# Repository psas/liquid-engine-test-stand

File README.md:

# liquid-engine-test-stand

# Liquid Fuel Engine Test Stand (LFETS) Project Overview

  PSAS team members have already designed and built a [2.5 kN regeneratively cooled bipropellant (liquid oxygen and ethanol) rocket engine](https://github.com/psas/liquid-engine-capstone-2015). This engine design included a number of innovative features including fully parametric CAD design using python scripts and SolidWorks, direct metal laser sintering (DMLS) additive manufacturing by i3D manufacturing, direct spark ignition and pintle injection. Although the rocket engine itself has already been produced, much of the overall system complexity lies in the piping, control, and data acquisition systems which support it. This project intends to flesh out these systems in order to test the engine and its successors.

  The test stand will safely test current and PSAS future generation liquid fuel engines prior to integration into a flight vehicle. PSAS will use the stand to measure engine performance, liquid fuel and oxidizer flow rates, propellant mixing capabilities and other engine performance figures of merit. These tests will be performed remotely, using automated valve switching and data acquisition systems. The LFETS system is designed to be portable by truck, and will support propulsion testing of engines up to 10 kN of thrust. The project will be open-source and will utilize live web-based Jupyter notebook design documentation.

  The feed system uses a classic regulated pressure-fed thermodynamic cycle. Gaseous nitrogen is the pressurant. The LFETS system includes a welded thrust loading truss structure, propellant and pressurant supply tanks, and feed system flow componentry. The project also includes safety and Failure Mode Effects Analysis, and procedures for safe operation and transport.
The LFETS Electrical Ground Support Equipment (EGSE) will allow for the test stand to be controlled remotely. The test stand computer controls all actuators in the LFETS system, auto-sequences engine ignition, start, shutdown, pad-safing, and contingency procedures for any test exception, as well as receiving telemetry from sensors and instrumentation. The LFETS EGSE system is derived from the 3rd generation [PSAS launch tower computer](https://github.com/psas/launch-tower), which uses a BeagleBone Black microcontroller, the [Marionette open-source DAQ](https://marionette-daq.github.io/), and a custom “SCADA-like” GUI.

## Useful Links

[CAD Files](https://github.com/psas/liquid-engine-test-stand/tree/master/cad/Test%20Stand%20CAD%20Files/current%20assembly)

[CAD Guide](https://github.com/psas/liquid-engine-test-stand/blob/master/cad/CAD%20Guide.pdf)

[Bill of Materials](https://drive.google.com/open?id=1SeBntyje6zpfy1jSxysdBP59IyhFcIg6SvVT6w5Bf4Y)

[PID](https://github.com/psas/liquid-engine-test-stand/tree/master/PID)

[Capstone Class Work](https://github.com/psas/liquid-engine-test-stand/tree/master/2018-2019%20Capstone%20documentation/Class%20papers%20and%20presentations)

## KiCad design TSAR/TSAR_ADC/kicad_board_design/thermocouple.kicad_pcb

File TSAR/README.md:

# TSAR
Test Stand Automation and Regulation system for the Portland State Aerospace Society's (PSAS) Liquid fuel engine test stand.

## New Member Onboarding

If you are interested in joining the TSAR team, please reference 'Onboarding.pdf' in the root of this repository. 

## Definitions

LFETS - Liquid fuel engine test stand

Module - Valves, sensors, the engine, the igniter. Anything that is a single moving, sensing or functional unit.

## Test Stand Automation and Regulation System Overview

The TSAR group will build an embedded controls and data acquisition system (CDAQ) for a liquid fuel rocket engine test stand for the Portland State Aerospace Society. Solving this issue is vital because developing a liquid fuel rocket engine will decrease PSAS’s cost per launch drastically while also opening the door for considerably higher peak apogees. Without the development of a safe CDAQ solution for the test stand, PSAS cannot reach its goals. The TSAR solution is a student led, in house solution which will create a custom taylored, safety oriented soluton for test stand CDAQ. Our solution is unique because it will be entirely open-sourced with a focus on repeatability and simplicity to allow other amateur rocket groups to benefit from the liquid rocket engine technology. We will use an off-the-shelf Beagle Bone Black embedded computer and a Marionette DAQ board (a former PSU capstone) to implement this system and all software will be developed by the TSAR team of PSU undergraduates.

Project Contact: Mark Musil - Junior in Electrical Engineering at Portland State University (mmusil@pdx.edu)

## Key Requirements

The following aspects of the system are mandatory. More details are present in the document 'TSAR_Requirements.docx' in the root of this repository. The core features are:

1. Interactive graphical dashboard for state control
2. Safety and security of the entire system
3. Clean, thorough documentation of all group efforts including well-commented code, photographic and videographic artifacts, and thorough usage and debugging resources. 

#### What are the major deliverables?
A graphical front end with safety features. A nervous system of sensors and actuators with realtime data output from the RPi3 to the front-end.

#### How will we get to those deliverables and the deadline?

Divison of the project into: 

High level application design - GUI, interactive LFETS diagram, state control, security features, real-time data output, data storage

Mid-level system architecture - Discretization of the firing sequence into states, designation of states for each module.

Low-Level sensor specification and sensing - Specification of each sensor's range, and performance characteristics and interfacing of the sensors and actuatuators with the marionette/Rpi3.

#### What are the milestones we need to hit?
October: assessment of each High,mid,low system requirements and the tools which will be used for each system.
November: Completed state-machine design, Front end specifications completed, sensor specifications completed.
December: Interface with the fuel sensor or other LFETS needs and provide data output for their project.
January: All sensors specified, all valves under control.
February: Interface with all sensors and have real-time, time alligned data output.
March: 
April:
May: Hot fire :)
#### Are there dependencies that could impact the timeline?

It is important that we allign with the needs of the test stand team's needs. In addition, we need to begin delivering a part's list to the Beta project people. 

## Critical Objectives in Temporal Order (To-do list)

1. ### Pre-design
	1. Team Orientation
		1. General Training
			- [] GitHub
			- [] Python Notebook
			- [] System Overview
	2. Task Distribution
		1. Sensor Acquisition and Interfacing
		2. Actuator Acquisiton and Interfacing 
		3. Beagle Bone Black to Actuators
		4. Marionette To sensors
		5. System Design 
		6. Front-End and GUI
		7. Networking
		8. Record Keeping and Documentation
2. ### Design Stage
	1. Consult with Doug Hall concerning System Design
	2. Meet with Jacob Tiller about sensor requirements
	3. Investigate tools such as PyQT
	4. Brainstorm
	5. Determine Critical Path
3. ### Prototyping Stage 1
	1. Develop skeletal prototype of each sub system
		1. Minimal working set for interfacing
	2. Build sensor to screen prototype.

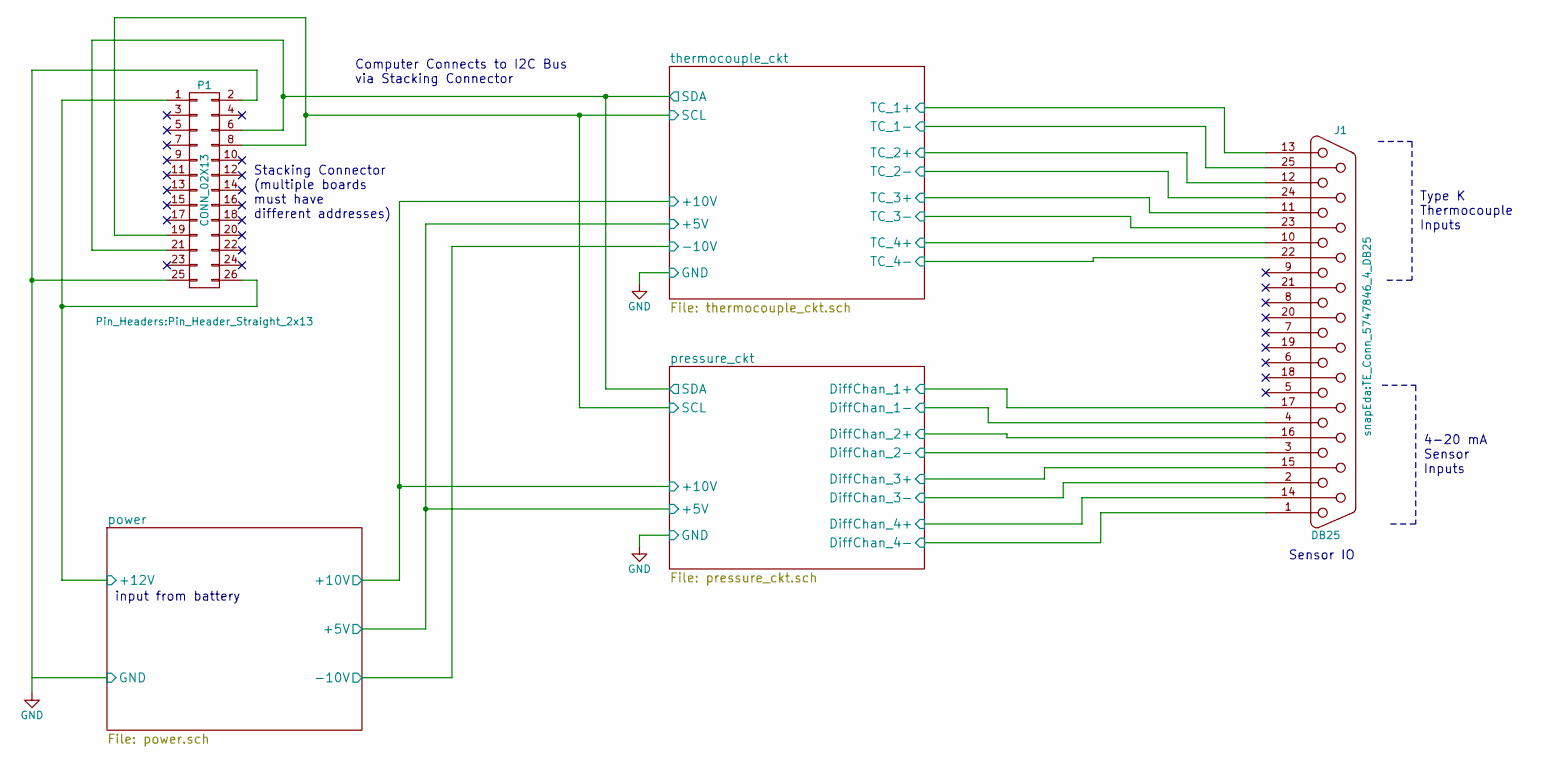
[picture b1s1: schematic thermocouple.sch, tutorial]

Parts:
J1: DB25; TE_Conn_5747846_4_DB25; MPN 5747846-4
P1: CONN_02X13; Pin_Header_Straight_2x13

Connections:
/power/+12V: P1.1, P1.26; also elsewhere on the board
/pressure_ckt/DiffChan_1+: J1.17; also elsewhere on the board
/pressure_ckt/DiffChan_1-: J1.4; also elsewhere on the board
/pressure_ckt/DiffChan_2+: J1.16; also elsewhere on the board
/pressure_ckt/DiffChan_2-: J1.3; also elsewhere on the board
/pressure_ckt/DiffChan_3+: J1.15; also elsewhere on the board
/pressure_ckt/DiffChan_3-: J1.2; also elsewhere on the board
/pressure_ckt/DiffChan_4+: J1.14; also elsewhere on the board
/pressure_ckt/DiffChan_4-: J1.1; also elsewhere on the board
/pressure_ckt/SCL: P1.8, P1.19; also elsewhere on the board
/pressure_ckt/SDA: P1.6, P1.21; also elsewhere on the board
/thermocouple_ckt/TC_1+: J1.13; also elsewhere on the board
/thermocouple_ckt/TC_1-: J1.25; also elsewhere on the board
/thermocouple_ckt/TC_2+: J1.12; also elsewhere on the board
/thermocouple_ckt/TC_2-: J1.24; also elsewhere on the board
/thermocouple_ckt/TC_3+: J1.11; also elsewhere on the board
/thermocouple_ckt/TC_3-: J1.23; also elsewhere on the board
/thermocouple_ckt/TC_4+: J1.10; also elsewhere on the board
/thermocouple_ckt/TC_4-: J1.22; also elsewhere on the board

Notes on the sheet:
Stacking Connector (multiple boards must have different addresses)
Sensor IO
input from battery
Type K Thermocouple Inputs
4-20 mA Sensor Inputs
Computer Connects to I2C Bus via Stacking Connector

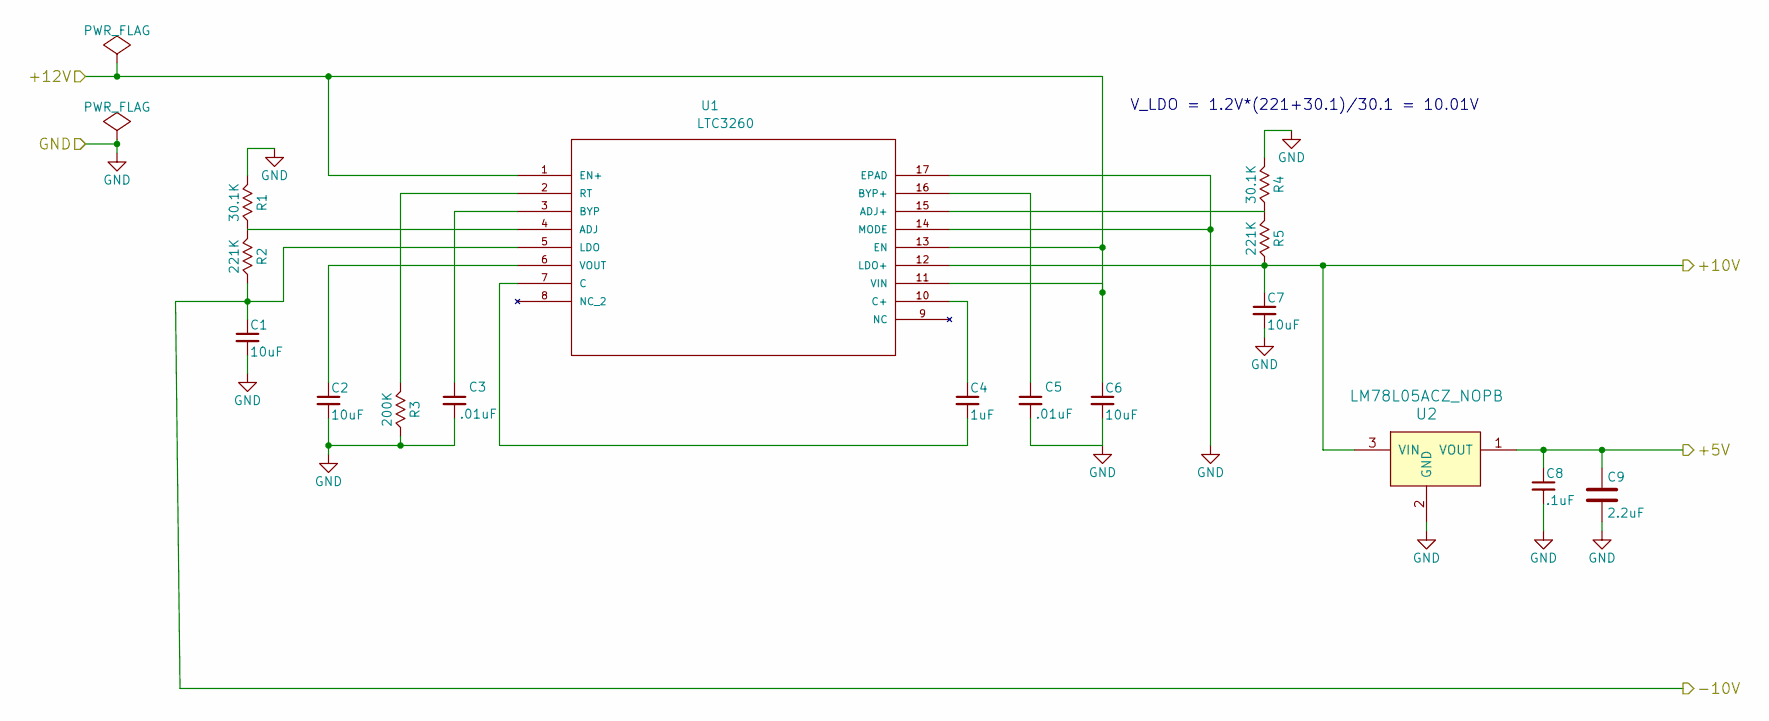
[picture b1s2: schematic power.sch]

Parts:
C1, C2, C6, C7: 10uF; C_0603_HandSoldering; MPN CL10B106MQ8NRNC
C3, C5: .01uF; C_0402; MPN CL05B103KB5NNNC
C4: 1uF; C_0603_HandSoldering; MPN CL10B105KP8NNNC
C8: .1uF; C_0402; MPN CL05B104KO54PNC
C9: 2.2uF; C_0805_HandSoldering; MPN C2012X7R1C225K125AB
R1, R4: 30.1K; R_0805_HandSoldering; MPN ERA-6AEB3012V
R2, R5: 221K; R_0805_HandSoldering; MPN ERA-6AEB2213V
R3: 200K; R_0805_HandSoldering; MPN KTR10EZPF2003
U1: LTC3260; MSOP-16_MSE; MPN LTC3260EMSE#PBF
U2: LM78L05ACZ_NOPB; TO-92-3; MPN LM78L05ACZ/NOPB; Digi-Key_PN LM78L05ACZNS/NOPB-ND

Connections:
/power/+5V: C8.1, C9.1, U2.1 (VOUT); also elsewhere on the board
/power/+10V: C7.1, R5.2, U1.12 (LDO+), U2.3 (VIN); also elsewhere on the board
/power/+12V: C6.1, U1.1 (EN+), U1.11 (VIN), U1.13 (EN); also elsewhere on the board
/power/-10V: C1.1, R2.2, U1.5 (LDO); also elsewhere on the board
unnamed: C2.1, U1.6 (VOUT)
unnamed: C3.1, U1.3 (BYP)
unnamed: C4.1, U1.10 (C+)
unnamed: C4.2, U1.7 (C)
unnamed: C5.1, U1.16 (BYP+)
unnamed: R1.2, R2.1, U1.4 (ADJ)
unnamed: R3.1, U1.2 (RT)
unnamed: R4.2, R5.1, U1.15 (ADJ+)

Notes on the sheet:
V_LDO = 1.2V*(221+30.1)/30.1 = 10.01V

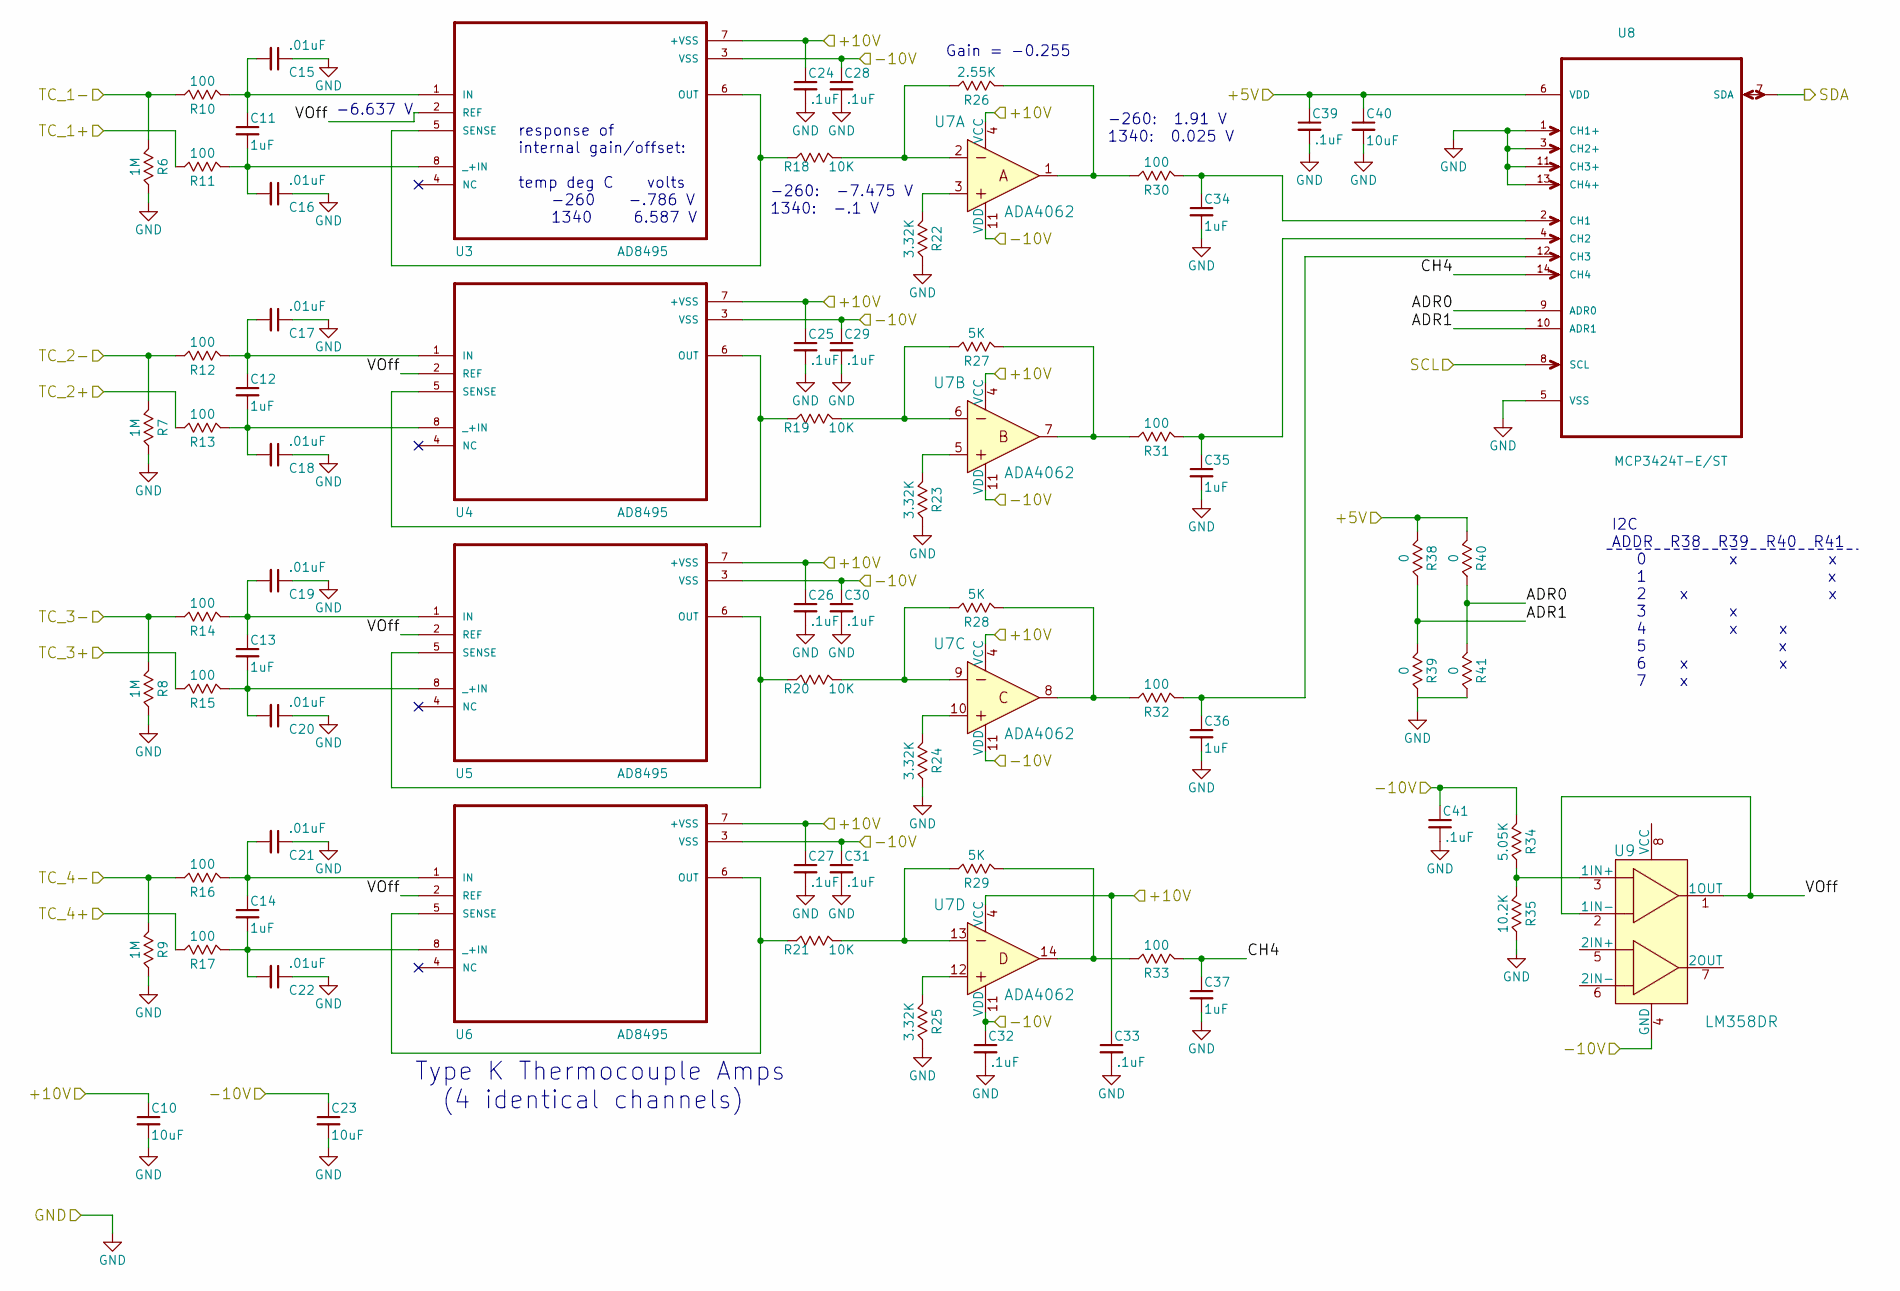
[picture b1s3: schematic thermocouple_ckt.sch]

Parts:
C10, C23, C40: 10uF; C_0603_HandSoldering; MPN CL10B106MQ8NRNC
C11, C12, C13, C14, C34, C35, C36, C37: 1uF; C_0603_HandSoldering; MPN CL10B105KP8NNNC
C15, C16, C17, C18, C19, C20, C21, C22: .01uF; C_0402; MPN CL05B103KB5NNNC
C24, C25, C26, C27, C28, C29, C30, C31, C32, C33, C39, C41: .1uF; C_0402; MPN CL05B104KO54PNC
R6, R7, R8, R9: 1M; R_0805_HandSoldering; MPN CRGH0805F1M0
R10, R11, R12, R13, R14, R15, R16, R17, R30, R31, R32, R33: 100; R_1206; MPN LTR18EZPF1000
R18, R19, R20, R21: 10K; R_0603_HandSoldering; MPN ERA-3ARB103V
R22, R23, R24, R25: 3.32K; R_0805_HandSoldering; MPN RR1220P-3321-D-M
R26: 2.55K; R_1206; MPN RT1206BRD075KL
R27, R28, R29: 5K; R_1206; MPN RT1206BRD075KL
R34: 5.05K; R_0603_HandSoldering; MPN RT0603DRE075K17L
R35: 10.2K; R_0805_HandSoldering; MPN RN73C2A10K2BTDF
R38, R39, R40, R41: 0; R_0805_HandSoldering; MPN ERJ-6GEY0R00V
U3: AD8495; SOP65P490X110-8N; MPN AD8495ARMZ-R7
U4, U5, U6: AD8495; SOP65P490X110-8N
U7: ADA4062; ADA4062-4ARUZ; MPN ADA4062-4ARUZ
U8: MCP3424T-E/ST; SOP65P640X120-14N
U9: LM358DR; SOIC-8_W3.9mm; MPN LM358DR; Digi-Key_PN 296-1014-1-ND

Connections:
/power/+5V: C39.1, C40.1, R38.1, R40.1, U8.6 (VDD); also elsewhere on the board
/power/+10V: C10.1, C24.1, C25.1, C26.1, C27.1, C33.1, U3.7 (+VSS), U4.7 (+VSS), U5.7 (+VSS), U6.7 (+VSS), U7.4 (VCC), U9.8 (VCC); also elsewhere on the board
/power/-10V: C23.1, C28.1, C29.1, C30.1, C31.1, C32.1, C41.1, R34.1, U3.3 (VSS), U4.3 (VSS), U5.3 (VSS), U6.3 (VSS), U7.11 (VDD), U9.4 (GND); also elsewhere on the board
/pressure_ckt/SCL: U8.8 (SCL); also elsewhere on the board
/pressure_ckt/SDA: U8.7 (SDA); also elsewhere on the board
/thermocouple_ckt/ADR0: R40.2, R41.1, U8.9 (ADR0)
/thermocouple_ckt/ADR1: R38.2, R39.1, U8.10 (ADR1)
/thermocouple_ckt/CH4: C37.1, R33.1, U8.14 (CH4)
/thermocouple_ckt/TCA_1: R18.2, U3.5 (SENSE), U3.6 (OUT)
/thermocouple_ckt/TCA_2: R19.2, U4.5 (SENSE), U4.6 (OUT)
/thermocouple_ckt/TCA_3: R20.2, U5.5 (SENSE), U5.6 (OUT)
/thermocouple_ckt/TCA_4: R21.2, U6.5 (SENSE), U6.6 (OUT)
/thermocouple_ckt/TC_1+: R11.2; also elsewhere on the board
/thermocouple_ckt/TC_1-: R6.1, R10.2; also elsewhere on the board
/thermocouple_ckt/TC_2+: R13.2; also elsewhere on the board
/thermocouple_ckt/TC_2-: R7.1, R12.2; also elsewhere on the board
/thermocouple_ckt/TC_3+: R15.2; also elsewhere on the board
/thermocouple_ckt/TC_3-: R8.1, R14.2; also elsewhere on the board
/thermocouple_ckt/TC_4+: R17.2; also elsewhere on the board
/thermocouple_ckt/TC_4-: R9.1, R16.2; also elsewhere on the board
/thermocouple_ckt/VOff: U3.2 (REF), U4.2 (REF), U5.2 (REF), U6.2 (REF), U9.1 (1OUT), U9.2 (1IN-)
unnamed: C11.1, C15.2, R10.1, U3.1 (IN)
unnamed: C11.2, C16.2, R11.1, U3.8 (_+IN)
unnamed: C12.1, C17.2, R12.1, U4.1 (IN)
unnamed: C12.2, C18.2, R13.1, U4.8 (_+IN)
unnamed: C13.1, C19.2, R14.1, U5.1 (IN)
unnamed: C13.2, C20.2, R15.1, U5.8 (_+IN)
unnamed: C14.1, C21.2, R16.1, U6.1 (IN)
unnamed: C14.2, C22.2, R17.1, U6.8 (_+IN)
unnamed: C34.1, R30.1, U8.2 (CH1)
unnamed: C35.1, R31.1, U8.4 (CH2)
unnamed: C36.1, R32.1, U8.12 (CH3)
unnamed: R18.1, R26.2, U7.2
unnamed: R19.1, R27.2, U7.6
unnamed: R20.1, R28.2, U7.9
unnamed: R21.1, R29.2, U7.13
unnamed: R22.1, U7.3
unnamed: R23.1, U7.5
unnamed: R24.1, U7.10
unnamed: R25.1, U7.12
unnamed: R26.1, R30.2, U7.1
unnamed: R27.1, R31.2, U7.7
unnamed: R28.1, R32.2, U7.8
unnamed: R29.1, R33.2, U7.14
unnamed: R34.2, R35.1, U9.3 (1IN+)
unnamed 91: U9.5 (2IN+); also elsewhere on the board

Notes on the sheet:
-6.637 V
response of internal gain/offset: temp deg C volts -260 -.786 V 1340 6.587 V
Type K Thermocouple Amps (4 identical channels)
Gain = -0.255
-260: -7.475 V 1340: -.1 V
-260: 1.91 V 1340: 0.025 V
I2C ADDR R38 R39 R40 R41 0 x x 1 x 2 x x 3 x 4 x x 5 x 6 x x 7 x

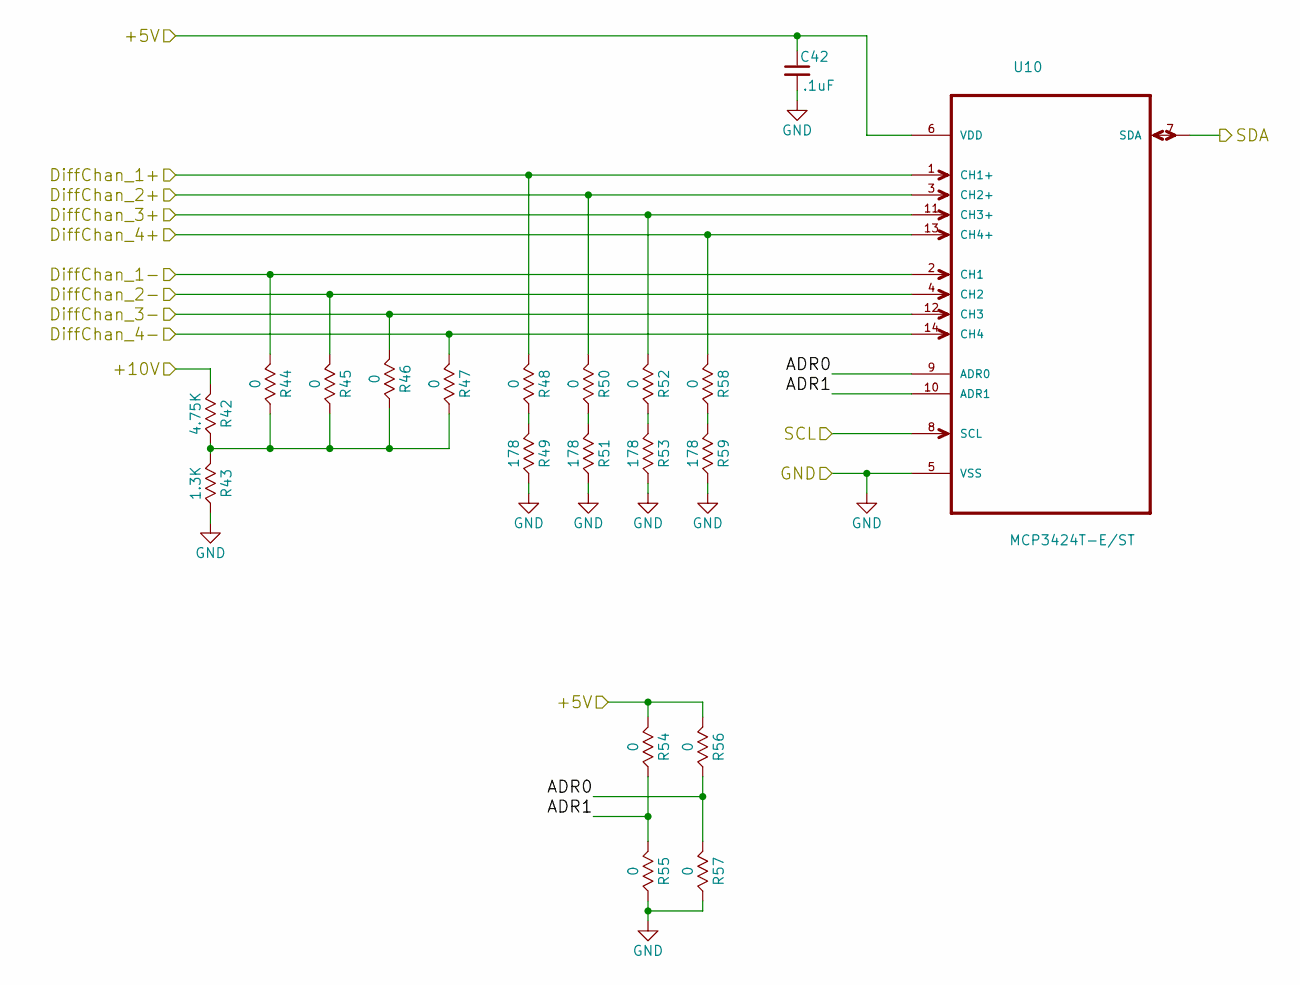
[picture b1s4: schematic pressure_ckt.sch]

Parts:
C42: .1uF; C_0402; MPN CL05B104KO54PNC
R42: 4.75K; R_0805_HandSoldering; MPN RG2012P-4751-B-T5
R43: 1.3K; R_0603_HandSoldering; MPN ERA-3APB132V
R44, R45, R46, R47, R48, R50, R52, R54, R55, R56, R57, R58: 0; R_0805_HandSoldering; MPN ERJ-6GEY0R00V
R49, R51, R53, R59: 178; R_0402; MPN ERA-2AEB1780X
U10: MCP3424T-E/ST; SOP65P640X120-14N

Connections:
/power/+5V: C42.1, R54.1, R56.1, U10.6 (VDD); also elsewhere on the board
/power/+10V: R42.1; also elsewhere on the board
/pressure_ckt/ADR0: R56.2, R57.1, U10.9 (ADR0)
/pressure_ckt/ADR1: R54.2, R55.1, U10.10 (ADR1)
/pressure_ckt/DiffChan_1+: R48.1, U10.1 (CH1+); also elsewhere on the board
/pressure_ckt/DiffChan_1-: R44.1, U10.2 (CH1); also elsewhere on the board
/pressure_ckt/DiffChan_2+: R50.1, U10.3 (CH2+); also elsewhere on the board
/pressure_ckt/DiffChan_2-: R45.1, U10.4 (CH2); also elsewhere on the board
/pressure_ckt/DiffChan_3+: R52.1, U10.11 (CH3+); also elsewhere on the board
/pressure_ckt/DiffChan_3-: R46.1, U10.12 (CH3); also elsewhere on the board
/pressure_ckt/DiffChan_4+: R58.1, U10.13 (CH4+); also elsewhere on the board
/pressure_ckt/DiffChan_4-: R47.1, U10.14 (CH4); also elsewhere on the board
/pressure_ckt/SCL: U10.8 (SCL); also elsewhere on the board
/pressure_ckt/SDA: U10.7 (SDA); also elsewhere on the board
unnamed: R42.2, R43.1, R44.2, R45.2, R46.2, R47.2
unnamed: R48.2, R49.1
unnamed: R50.2, R51.1
unnamed: R52.2, R53.1
unnamed: R58.2, R59.1

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
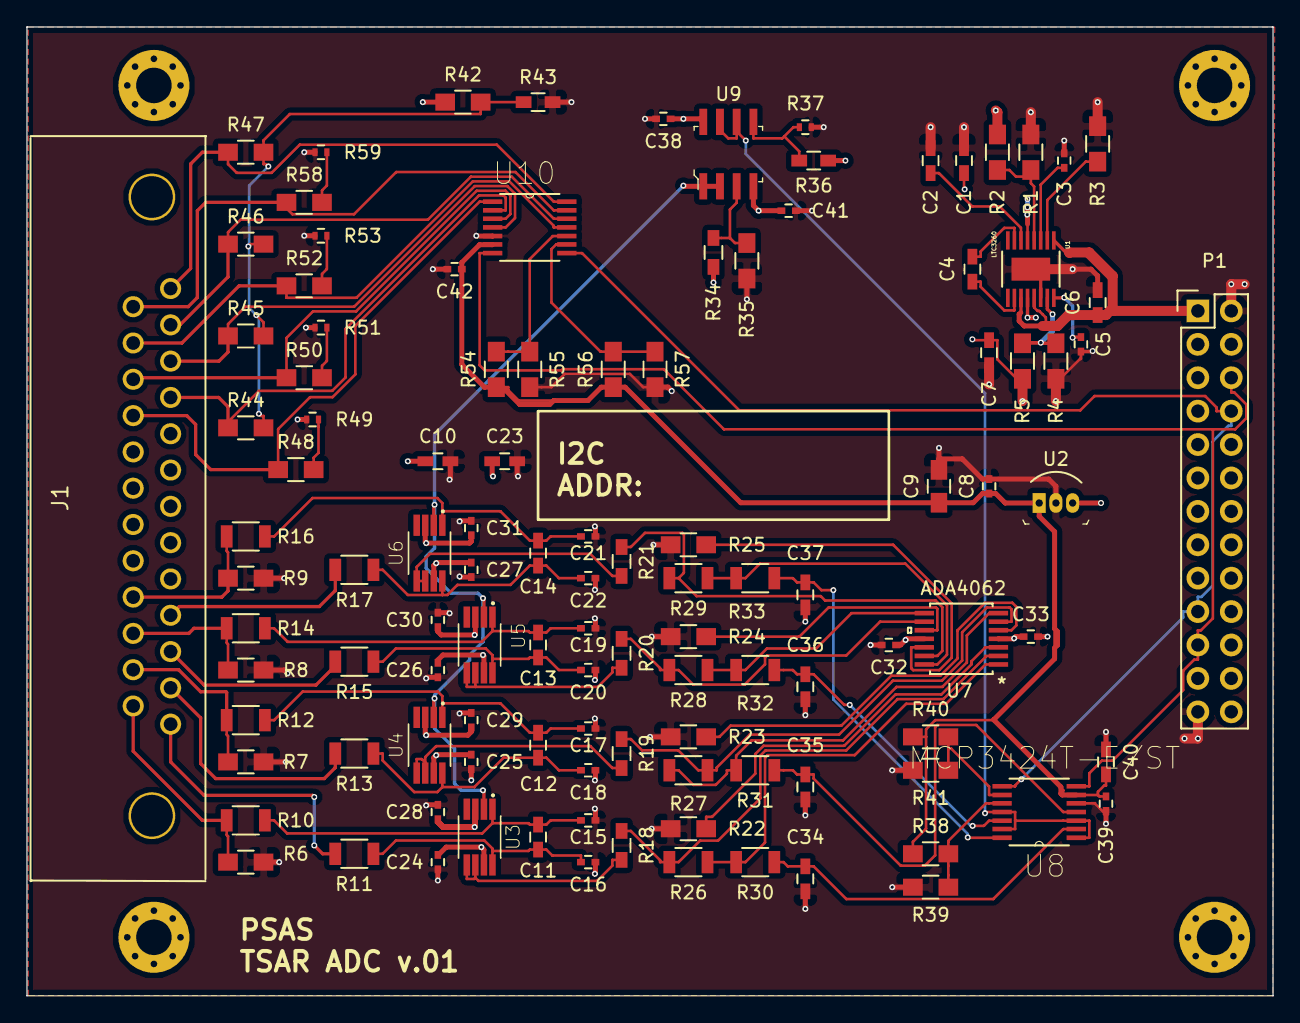
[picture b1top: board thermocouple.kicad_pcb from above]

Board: 4 copper layers, 94.7 x 73.7 mm, 117 parts (0 on the bottom side), 72 nets.

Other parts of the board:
C38: .1uF; C_0402
R36: 11.1K; R_0603_HandSoldering
R37: 2.55K; R_0402
REF1, REF2, REF3, REF4: MountingHole_2.7mm_M2.5_Pad_Via

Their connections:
/power/+10V: C38.1, R36.1; also elsewhere on the board
unnamed 91: R36.2, R37.1; also elsewhere on the board

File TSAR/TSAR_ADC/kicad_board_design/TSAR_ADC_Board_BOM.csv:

Refs,Value,Footprint,Quantity,MFR,MPN,SPR,SPN
C3;C5,.01uF,Capacitors_SMD:C_0402,2,Samsung,CL05B103KB5NNNC,Digikey,1276-1028-1-ND
C8,.1uF,Capacitors_SMD:C_0402,1,Samsung,CL05B104KO54PNC,Digikey,1276-6995-1-ND
C1;C2;C6;C7,10uF,Capacitors_SMD:C_0603_HandSoldering,4,Samsung,CL10B106MQ8NRNC,Digikey,1276-1948-1-ND
C4,1uF,Capacitors_SMD:C_0603_HandSoldering,1,Samsung,CL10B105KP8NNNC,Digikey,1276-1946-1-ND
C9,2.2uF,Capacitors_SMD:C_0805_HandSoldering,1,TDK,C2012X7R1C225K125AB,Digikey,445-1420-1-ND
U1,LTC3260,MSOP-16_MSE,1,Linear Tech,LTC3260EMSE#PBF,Digikey,LTC3260EMSE#PBF-ND
R3,200K,Resistors_SMD:R_0805_HandSoldering,1,Rohm,KTR10EZPF2003,Digikey,RHM200KAHCT-ND
R2;R5,221K,Resistors_SMD:R_0805_HandSoldering,2,Panasonic,ERA-6AEB2213V,Digikey,P221KDACT-ND
R1;R4,30.1K,Resistors_SMD:R_0805_HandSoldering,2,Panasonic,ERA-6AEB3012V,Digikey,P30.1KDACT-ND
U2,LM78L05ACZ_NOPB,digikey-footprints:TO-92-3,1,Texas Instruments,LM78L05ACZ/NOPB,Digikey,LM78L05ACZNS/NOPB-ND
,,,,,,,
C42,.1uF,Capacitors_SMD:C_0402,1,Samsung,CL05B104KO54PNC,Digikey,1276-6995-1-ND
R49;R51;R53;R59,178,Resistors_SMD:R_0402,4,Panasonic,ERA-2AEB1780X,Digikey,P178DCCT-ND
R43,1.3K,Resistors_SMD:R_0603_HandSoldering,1,Panasonic,ERA-3APB132V,Digikey,P1.3KAYCT-ND
R44;R45;R46;R47;R48;R50;R52;R58;R56;R54;R55;R57,0,Resistors_SMD:R_0805_HandSoldering,12,-,ERJ-6GEY0R00V,Digikey,P0.0ACT-ND
R42,4.75K,Resistors_SMD:R_0805_HandSoldering,1,Susumu,RG2012P-4751-B-T5,Digikey,RG20P4.75KBCT-ND
U11,MCP3424T-E/ST,SOP65P640X120-14N,1,Microchip,-,Digikey,MCP3424T-E/STCT-ND
,,,,,,,
C22;C21;C20;C19;C18;C17;C15;C16;C3;C5,.01uF,Capacitors_SMD:C_0402,10,Samsung,CL05B103KB5NNNC,Digikey,1276-1028-1-ND
C27;C26;C30;C25;C29;C24;C28;C31;C32;C33;C38;C41;C39;C42;C8,.1uF,Capacitors_SMD:C_0402,15,Samsung,CL05B104KO54PNC,Digikey,1276-6995-1-ND
C10;C23;C40;C1;C2;C6;C7,10uF,Capacitors_SMD:C_0603_HandSoldering,7,Samsung,CL10B106MQ8NRNC,Digikey,1276-1948-1-ND
C14;C13;C12;C11;C37;C36;C35;C34;C4,1uF,Capacitors_SMD:C_0603_HandSoldering,9,Samsung,CL10B105KP8NNNC,Digikey,1276-1946-1-ND
P1,CONN_02X13,Pin_Headers:Pin_Header_Straight_1x13,1,-,-,-,-
R37,2.55K,Resistors_SMD:R_0402,1,Panasonic,ERA-2ARC2551X,Digikey,P18212CT-ND
R18;R19;R20;R21,10K,Resistors_SMD:R_0603_HandSoldering,4,Panasonic,ERA-3ARB103V,Digikey,P10KBDCT-ND
R36,11.1K,Resistors_SMD:R_0603_HandSoldering,1,Stackpole Electronics,RNCF0603BTE11K1,Digikey,RNCF0603BTE11K1CT-ND
R34,5.17K,Resistors_SMD:R_0603_HandSoldering,1,Yageo,RT0603DRE075K17L,Digikey,311-2631-1-ND
R38;R40;R41;R39;R44;R45;R46;R47;R48;R50;R52;R58;R56;R54;R55;R57,0,Resistors_SMD:R_0805_HandSoldering,16,-,ERJ-6GEY0R00V,Digikey,P0.0ACT-ND
R35,10.2K,Resistors_SMD:R_0805_HandSoldering,1,TE Connectivity,RN73C2A10K2BTDF,Digikey,A103283TR-ND
R6;R7;R8;R9,1M,Resistors_SMD:R_0805_HandSoldering,4,TE Connectivity,CRGH0805F1M0,DIgikey,A126423CT-ND
R22;R23;R24;R25,3.32K,Resistors_SMD:R_0805_HandSoldering,4,Susumu,RR1220P-3321-D-M,Digikey,RR12P3.32KDCT-ND
R10;R30;R11;R12;R13;R14;R15;R16;R17;R31;R32;R33,100,Resistors_SMD:R_1206,12,Rohm,LTR18EZPF1000,Digikey,RHM100YCT-ND
R26;R27;R28;R29,5K,Resistors_SMD:R_1206,4,Yageo,RT1206BRD075KL,Digikey,YAG5090CT-ND
U3;U4;U5;U6,AD8495,SOP65P490X110-8N,4,Analog Devices,AD8495ARMZ,Mouser,584-AD8495ARMZ
U9,MCP3424T-E/ST,SOP65P640X120-14N,1,-,-,Digikey,MCP3424T-E/STCT-ND
U10,LM358DR,digikey-footprints:SOIC-8_W3.9mm,1,Texas Instruments,LM358DR,Digikey,296-1014-1-ND
J1,CONN D-SUB RCPT 25POS R/A SOLDER,snapEda:TE_Conn_5747846_4_DB25,1,TE Connectivity,5747846-4,Digikey,A32126-ND
U7,ADA4062,snapEda:ADA4062-4ARUZ,1,Analog Devices,ADA4062-4ARUZ,Digikey,ADA4062-4ARUZ-ND

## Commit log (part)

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2016-06-23 added a start towards pressurant tank volume calculation
2016-06-23 added some more variables, still quite rough
2016-06-23 not clean or pretty, but working with spoofed numbers
2016-07-06 Moved PID files into their own directory.
2016-07-06 Adding whiteboard scribble from conversation with Andrew. Illustrates expected connections between sensors, the DAQ, the LTC, a testing laptop, and a dashboard UI.
2016-07-18 Add files via upload
    PID with fitting level detail. -KJM
2016-08-02 Fixed some syntax errors
2016-08-23 reorganized, added current PID
2016-08-31 updated CAD layout
2016-09-09 Test Stand Assembly Updated
2016-09-09 Revert "Test Stand Assembly Updated"
    This reverts commit b79e00b5652df4786d6530549077c322bd3dee19.
2016-09-09 Revert "Revert "Revert "Test Stand Assembly Updated"""
    This reverts commit ef1ff43956c0bee73f7367af25b080eca4fa811c.
2016-09-21 Added Test Stand Components)
2016-10-26 Moving the Igniter folder for organizational purposes
2016-10-26 Forgot to add gitignore
2016-11-16 added pdf files of load cell support drawings
2016-11-30 adding component spec sheets
2017-02-05 PID now drawn as svg file in inkscape. Several small updates made, but the PID needs to be reviewed against the BOM. Several parts appear to be mis numbered or incorrectly labelled.
2017-02-06 Cosmetic updates to PID. Still needs full review against BOM
2017-02-22 updating files CAD files
2017-02-23 added test stand image for readme
2017-03-07 PID update, still in progress
2017-03-07 started a more detailed pressure budget calculation
2017-03-09 reorganized repo file structure
2017-03-09 added readme for igniter repo, some other organization
2017-03-09 grammar fix
2017-03-11 updated fittings level PID. Still need to spec a few components and integrate igniter PID.
2017-03-11 minor reorganization of files
2017-03-25 adding gratuitous flow chart (GFC) in svg and pdf
2017-03-25 Add files via upload
    Cleaning Procedure for parts in contact with LOX. Still needs a procedure for using the ultrasonic cleaner, as well as a designated "clean parts" area in the lab.
2017-03-27 get rid of annoying windows cache files
2017-03-31 More PID updates, Updated System level PID to be reasonably complete
2017-04-27 Update README.md
    Added preliminary project breakdown to read me and began linking current issues to it.
2017-05-12 Started diffuser calculations, rest waiting on details
2017-05-22 Added a couple bits of info on the tanks and fittings
2017-06-04 Added dummy pressurant diffuser to edit with proper geometry and thread
2017-07-09 12VDC_valve_assembly initial upload
2017-07-09 removing temporary files.
2017-07-09 Bad logic
2017-07-10 Fixed encoding wheel logic and updated readme
2017-07-11 Updated image
2017-07-11 Updating rotor, shaft assembly & parts
2017-07-11 07.10.2017 added hardware and fixed LED pattern drawing (over-defined)
2017-07-11 added initial driver file.
2017-07-16 07_15_2017 More DC Motor Mount CAD work.
2017-07-16 DC Motor mount updating
2017-07-24 12VDC MFV Updated assembly and some files
2017-07-26 Adding SOP template copy of launch 12 procedure book
2017-08-02 Finalized DC Motor housing front and back pieces. Ready for printing.
2017-08-06 Updated 12VDC housing and assembly to final for printing. Added housing back and front.
2017-09-09 added documentation to BOM
2017-09-11 Changed git ignore
2017-09-20 Moved igniter resources to a separate folder and added a jupyter notebook to begin calculations.
2017-09-20 Updating with removed external resources for igniter
2017-09-20 Updating ingiter calculations notebook.
2017-09-27 Added Science file
2017-09-27 Updated Arduino driver for 12VDC Main Fuel Valve control. Back to basics...
2017-10-10 some work on igniter calculations, more work to do
2017-10-10 More work on Igniter Calculations, more to do
2017-10-12 igniter calc additions
2017-10-12 some housekeeping
2017-10-15 minor updates to igniter calculations, more updates needed
2017-10-18 igniter calculation work
2017-10-18 Moved around some schtuff
2017-10-27 updated readme and onboarding
2017-11-01 Updated BOM with changes relevant to pressure panel.
2017-11-01 Updated BOM with Pressure Panel relevant changes
2017-11-05 minor update to PID
2017-11-05 test commit for new computer
2017-11-15 Added better BOM
2017-11-15 Restoring igniter documentation
2017-11-15 some igniter calculation updates
2017-11-15 updating PID spec'd xducers
2017-11-16 Cleaning up BOM
2017-11-17 Update BoM
2017-11-22 minor updates
2017-11-22 restoring igniter calcs
2017-11-22 update igniter calc with oxfuel mass ratio
2017-11-22 added updated PDF of PID, removed outdated versions
2017-11-23 Added firing sequence flow chart, gannt chart
2017-12-12 housekeeping
2017-12-12 Added some readme files to Main Fuel Valve
2017-12-31 Added thermocouple driver code
2018-01-02 some igniter calc work
2018-01-05 Added whiteboard image of brainstorming sess.
2018-01-07 update to igniter calculations
2018-01-15 Added Jan12_2018
2018-01-19 Weekly notes
2018-01-24 Created modified fuel tank top plate for machining. Place in new cad folder.
2018-01-26 Added Jan 25 TSAR meeting notes
2018-02-09 Added Weekly Meeting Notes
2018-03-04 added working PT code
2018-03-04 added readme for the pressure transducer
2018-03-04 Added circuit diagram for the pressure transducer
2018-04-02 Updated folder names under DC MFV
2018-04-02 Added readme to 12VDC valve driver folder
2018-08-19 Updated placeholder PIDs with system specific simplified versions (Except Enginge)
2018-08-19 updated in inkscape to make bg visible
2018-08-19 Updated shell script to reflect required install in linux.
2018-08-19 Updated gitignore
2018-09-21 Change from screw terminal block to DB-25.
2018-11-06 Simplify thermocouple signal chain for better worst case.
2018-11-08 trying out ecosystem on git
2018-11-12 Updated Test Stand CAD
2018-11-21 Incorporate review comments. Improve U1 routing, general schematic comments.
2019-01-06 New test stand assembly, old moved to "2016" new in "current_assembly"
2019-01-15 Adding Data From First Calibration Tests
    Flow and pressure calibration data added. Also some changes to the pintle test das.
2019-01-16 added some graphs for the flow meter
2019-01-20 Pintle Test Data Added
    Under Analysis folder
2019-01-22 begain data analysis for pintle test
2019-01-28 added data for pinlte test from 26 jan 18
2019-02-11 update of image
2019-02-11 testing image link for notebook
2019-02-16 updates to the pintle test post mortem and pintle V1 calculations
2019-02-17 updates to the pintle test post mortem
2019-02-18 Redlined PID
2019-02-18 CAD post review update
    CAD updates after review
    2/17/2019
2019-02-19 small tweak to image size in pintle post mortem.
2019-02-19 testing image resizing in git
2019-02-20 fixed image link
2019-02-20 testing text centering
2019-02-23 More work on Pintle Post Mortem report and calculations
2019-02-23 Updates to 00 Pintle Post Mortem
2019-02-23 fixed some typos and started Pintle V2 design notebook
2019-02-23 Added calculations for loss coefficients to Pintle V1 post mortem
2019-02-25 Added Pintle V1 and V2 CAD
2019-03-20 TEST - CAD upload
2019-03-21 CAD Update - Fittings reviewed
2019-04-02 Test Stand CAD update
    Updated fittings for all necessary sections
2019-04-04 Updating gitignore for future project.
2019-04-08 Some updates to the Pintle flow equations
2019-04-10 CAD fittings update
    More fittings added, all sections complete. Added flared tube end. Beginning piping.
2019-04-11 Adding pressure-reservoir calculations
2019-04-11 CAD update
    Flared ends added to AN fittings
2019-04-15 CAD Preliminary Piping
    All piping for available sections added and is ready for review.
2019-04-18 Added Venturi CAD to test stand CAD
2019-04-23 Integrated new igniter system
    New igniter system added to main test stand CAD
2019-04-24 Added diffuser and pressure reservoir notebooks
2019-04-25 Adding diffuser calcs
2019-04-30 reorganized the pintle design files
2019-05-02 test stand CAD update
    Real venturis added to main test stand CAD. Begining piping
2019-05-03 main test stand CAD update
    all piping until bulkhead has been completed.
2019-05-06 CAD fitting update
2019-05-07 CAD piping update
    adjustments made to intial straight lengths of pipes to account for fitting assembly
2019-05-12 CAD upper fuel section update
2019-05-14 pipe drawing PDF made
2019-05-15 Main fuel valve CAD added
    Added main fuel valve placeholder
2019-05-16 Piping and order update
    Updated LOX side piping to account for manufacturing procedures along with updating the drawings to be sent out for manufacturing.
2019-05-22 updates to the Pintle design documents and initial raw data from pintle V3 hydro testing
2019-05-23 CAD update
    Update to LOX side pipes with the addition of new fittings. Revised format for pipe drawings also.
2019-05-27 Updtes to pintle design tool
2019-05-28 CAD preliminary final version
    Updated fittings, added nuts and sleeves, adjusted some piping
2019-05-29 updates to pintle design documents
2019-05-29 testing equation display fix on documentation
2019-05-29 maybe fixed incorrectly displaying equations issue
2019-05-30 CAD final update
    update main fuel and lox valves
2019-06-02 updates to pintle design document
2019-06-18 some reorganization
2019-06-18 Add Igniter Design Documentation
2019-06-18 Re-organized some files
2019-06-18 Updating with MFV actuator CAD files
2019-06-19 Cleaning up and collecting analysis documents to a single folder.
2019-06-19 Consolidating minor analysis to a single folder.
2019-07-09 added magnetic sensor read code
2019-07-09 adapter board updates
2019-07-27 add new PID to git
2019-07-30 update to test code
2019-07-31 folder cleanup
2019-10-27 2019-10-27 LFETS P&ID.drawio
2019-11-20 added link to doc
2020-01-18 Add 2019-2020 version
2020-01-25 Started to organize files to create new assembly
2020-01-29 Work on test stand assembly
    + adding in more valves, mocked up an actuated valve
2020-01-29 updated notes
2020-01-30 pressure panel update
2020-02-15 updates to stand assembly
2020-02-15 fuel manifold assembly work
2020-02-16 more fuel side work
2020-04-17 delete the test!
    why did you do that?!
2020-04-27 N2 node work
2020-04-30 a few screenshots
    they are of the stupid (hard) way to create dimension
2020-05-01 More N2 work
2020-05-01 N2 node work
    Completed valve layout
2020-05-01 n2 work continues
2020-05-02 routing_tutorial_part_deux
    things to do:
    create tubing templates (.5 OD and .75 OD)
2020-05-02 more work from routing tutorial part deux
2020-05-07 LOX fill tubing
    added tubing, fittings, and valves for the LOX fill side of the test stand.
    the flange on the bottom is a place holder for a more attractive interface with the LOX dewar
2020-05-07 fixed some crap, broke some crap
    too many questions... for 5/7 meeting
2020-05-18 sunday session
2020-05-18 bit more
2020-05-19 getting close
2020-05-21 getting ready to make review changes
2020-05-24 saving work
2020-05-25 stopping point
    did a pack and go to clean up the files
2020-05-26 organize CAD in SW
    prep for presentation video
2020-06-11 handoff meeting 6/11/2020
2020-07-15 Load Cell Replacment
    Makeshift load cell blocks were replaced with spacers for the new FC23 load cell. Bolts to attach FC23 to spacers are missing, parts left floating to indicate the bolt holes are unfinished.
2020-07-28 Finished redesign of load cell assembly
    Finished redesign of load cell assembly to accomodate the new FC23 load cells.
2020-08-05 Load cell assembly work
    Added screws to fasten the load cell to the the spacer.
2020-08-11 File name change
    Changed name of load cell assembly file.
2020-09-16 Archiving old work to reduced confusion
    First pass moving out of date, abandoned or otherwise not longer relevant project files into the Archive folder. Please let me know if you can't find something.
2020-12-31 CAD Work
    Added Load Cell Assembly to LFETS Assembly
    Added notes to LFETS Assembly
2021-01-03 CAD work
    Added new V3 pintle to engine
2021-01-04 Load Cell drawings
    Created drawing of load cell for LFE work

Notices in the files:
parts and their libraries:
Copyright 2016 Accelerated Designs. All rights reserved.
